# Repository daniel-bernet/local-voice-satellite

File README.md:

# Local Voice Satellite

A DIY voice satellite for [Home Assistant](https://www.home-assistant.io/): an ESP32-S3 with an I²S microphone, an I²S amplifier and an LED ring in a 3D-printed case. The wake word runs on the device. Speech-to-text and text-to-speech run on my own server. No audio goes to a cloud service.

<!-- PHOTO NEEDED: images/v2-hero.jpg: the assembled V2 satellite on a plain desk, LED ring lit amber, 3/4 front view from slightly above, neutral background, nothing else in frame. Replaces the render above. -->

This is a **portfolio showcase and a reference design**, not a kit. It documents one working build and the reasoning behind it: what I chose, why, what broke and what I'd do differently. It's meant for people who want to build something similar and are happy to make their own decisions. It is not a step-by-step tutorial.

## Why

I wanted a voice assistant for my home that works like a smart speaker but stays private: no always-listening cloud device, and no recordings leaving the house. Home Assistant's voice pipeline makes that possible with local speech-to-text and text-to-speech. What was missing was a satellite I understood end to end and could repair, so I built one.

## Result

The V2 satellite works. It hears "Hey Jarvis" on the device, Home Assistant turns the request into text and the answer into speech locally, and the answer plays on the satellite while the LED ring shows each stage. Simple requests take about 5–10 s end to end, down from about a minute right after assembly. I haven't measured the stage times yet. What V2 taught me (a mic mount that broke under the wire forces, speaker hiss, LEDs without a level shifter) went into a V3 PCB and case, which are designed and checked in code only, not built.

## Status

| Part | Status |
|---|---|
| **Satellite V2 (hand-wired)**: perfboard electronics in the V2 case | Built by me, working. Wake word, answers and audio all work. |
| **V2 enclosure** | Printed and assembled. Everything fit. |
| **V2 firmware** (ESPHome) | Running on the V2 satellite. The published copy is sanitised and passes ESPHome's config validation (2026.10.2). |
| **Satellite V3 (custom PCB)** | **Unverified design (rev A).** Designed, not fabricated, not tested, and it may never be built. Only code-level checks were run ([details](hardware/v3-pcb/README.md#what-was-checked)). |
| **V3 enclosure** | Unverified design, never printed. |
| **V3 firmware** | Draft for the unbuilt board. Passes ESPHome's config validation, never flashed. |
| **Voice pipeline**: on-device wake word, local STT (Whisper) and TTS (Piper) | Working. Observed end-to-end latency for simple requests (time, weather): **about 5–10 s**, down from about 1 min right after assembly. The stage times haven't been measured yet. |
| **LLM agent** for open questions | **Planned.** Not connected yet. |

### Next steps
- Measure the stage times (wake → end of speech → STT → intent → TTS) in Home Assistant's pipeline debug view, and only then decide what to optimise.
- Connect an LLM agent behind Home Assistant's built-in intents.
- Decide whether V3 gets built. If it does, start with the [must-verify list](hardware/v3-pcb/README.md#must-verify-before-ordering).

## Features

- **On-device wake word** ("Hey Jarvis", [micro_wake_word](https://esphome.io/components/micro_wake_word/)). Audio only streams to Home Assistant after the wake word.
- **Fully local pipeline**: Whisper for speech-to-text and Piper for text-to-speech, through Home Assistant's [Wyoming](https://www.home-assistant.io/integrations/wyoming/) integration.
- **LED ring state machine**: breathing while listening, a circling comet while thinking, a soft glow while answering, a red blink on errors and dim red while Home Assistant is disconnected. Every stage has a timeout, so the ring can't hang.
- **Amplifier power gating**: the amp's shutdown pin is driven by the firmware, so the speaker is silent between answers (no idle hiss).
- **Sealed speaker chamber** with TPU gaskets, the speaker firing upwards through a grille, and the mic on the front wall at 90° to it.
- **Designed as code**: the case is parametric [build123d](https://github.com/gumyr/build123d) code with automated collision, seal and assembly checks. The V3 PCB is generated by a Python toolkit into a KiCad 9 project.

## Architecture

```mermaid
flowchart LR
    subgraph SAT["Satellite (ESP32-S3)"]
        MIC["I²S mic"] --> WW["Wake word<br/>(micro_wake_word)"]
        LED["LED ring<br/>state machine"]
        SPK["I²S amp + speaker"]
    end
    WW -- "audio after wake word<br/>(ESPHome API, encrypted)" --> HA["Home Assistant<br/>Assist pipeline"]
    HA --> STT["Speech-to-text<br/>Whisper (Wyoming)"]
    STT --> INT["Built-in intents<br/>(time, weather, devices)"]
    INT -. "unmatched requests<br/>(planned)" .-> LLM["LLM agent<br/>(planned)"]
    INT --> TTS["Text-to-speech<br/>Piper (Wyoming)"]
    LLM -.-> TTS
    TTS -- "answer audio" --> SPK
    HA -- "pipeline events" --> LED
```

The diagram shows roles, not machines. More in [docs/architecture.md](docs/architecture.md).

## Hardware at a glance (V2, the working build)

| Part | Notes |
|---|---|
| ESP32-S3 devkit, N16R8 (16 MB flash, 8 MB octal PSRAM) | micro_wake_word needs the PSRAM |
| INMP441 I²S MEMS mic breakout (round) | I²S bus 0. End of life; the ICS-43434 is the usual replacement |
| MAX98357A I²S class-D amp breakout | I²S bus 1, gain 9 dB (GAIN pin open) |
| 40 mm full-range speaker | 40 × 40 mm flange, 32 mm hole pitch |
| WS2812B strip, 144 LED/m, 5 V | 40 LEDs (about 28 cm) around the inside of a clear plinth |
| USB-C PD trigger board, set to 5 V | one 5 V / GND star point for every module |
| 40 × 60 mm perfboard, 2 electrolytics (470 µF, 1000 µF), 10 kΩ × 2, 330 Ω | |
| M3 button-head screws (ISO 7380): 5 × M3×10, 4 × M3×8, 4 × M3×20 | threaded straight into PETG, no inserts |
| Filament: PETG black, PCTG clear, TPU black | printed on a Bambu Lab A1 mini, 0.4 mm nozzle |

Wiring diagram and pin table: [hardware/v2](hardware/v2/README.md). The V3 BOM with part numbers is in [hardware/v3-pcb/bom.csv](hardware/v3-pcb/bom.csv).

## Build and run

Tested with Python 3.12 and ESPHome 2026.10.2, from the repository root. The generators rewrite the committed outputs in place.

```bash
# Firmware: validate the V2 config. In secrets.yaml, replace the placeholder API key with a
# generated one (the command is in the file) and fill in your Wi-Fi details.
pip install esphome
cp firmware/esphome/secrets.example.yaml firmware/esphome/secrets.yaml
esphome config firmware/esphome/voice-satellite-v2.example.yaml

# V3 PCB (unverified design): regenerate, then read the outputs back with independent parsers
pip install shapely numpy matplotlib gerbonara kiutils
python3 hardware/v3-pcb/source/satellite_v3_pcb.py
python3 hardware/v3-pcb/source/check_outputs.py

# Cases: regenerate and check (V3 reads the board geometry written by the PCB step)
pip install build123d trimesh pyvista networkx
python3 enclosure/v2/source/case_v2.py && python3 enclosure/v2/source/check_case_v2.py
python3 enclosure/v3/source/case_v3.py && python3 enclosure/v3/source/check_case_v3.py
```

Flashing and adopting the device in Home Assistant: [firmware/esphome](firmware/esphome/README.md). Printing and assembly: [enclosure](enclosure/README.md) and [build notes](docs/build-notes.md). What reproduces exactly and what doesn't: [enclosure](enclosure/README.md#regenerate) and [V3 PCB](hardware/v3-pcb/README.md#files).

## Repository map

| Path | What's in it |
|---|---|
| [docs/](docs/) | [architecture](docs/architecture.md) · [design decisions](docs/design-decisions.md) · [wiring](docs/wiring.md) · [build notes](docs/build-notes.md) · [lessons learned](docs/lessons-learned.md) · [how it was built](docs/how-it-was-built.md) |
| [hardware/v2/](hardware/v2/README.md) | Hand-wired V2: wiring diagram (SVG) and pin table |
| [hardware/v3-pcb/](hardware/v3-pcb/README.md) | Custom PCB, **unverified rev A**: generator source, KiCad 9 project, Gerbers, BOM, renders, check report |
| [enclosure/](enclosure/README.md) | V2 (built) and V3 (unverified) cases: CAD source, STL in print orientation, STEP, renders, print settings |
| [firmware/esphome/](firmware/esphome/) | ESPHome example configs for V2 and V3 and a `secrets.example.yaml` |
| [images/](images/) | Photos (EXIF stripped) |

## How it was built

This project was built with AI assistance (Claude by Anthropic). I defined the requirements, chose the components, measured the real parts, specified and reviewed the designs, and printed, soldered, assembled and tested the hardware. The enclosure and the V3 PCB were generated **as code with AI assistance**, and the firmware, the wiring and soldering guides, the wiring diagram and the doc drafts were written with AI support. I reviewed, adapted and tested all of it. The full split of who did what is in [docs/how-it-was-built.md](docs/how-it-was-built.md).

## Licence

This is open source and permissive: you can copy, modify and sell it, as long as you keep the copyright and licence notices.

| What | Licence |
|---|---|
| Firmware configs and all code, including the PCB and CAD generators and check scripts (`firmware/`, `hardware/v3-pcb/source/`, `enclosure/*/source/`, except Markdown files) | [MIT](LICENSE) |
| Hardware designs: PCB, KiCad project, Gerbers, BOM, STL/STEP, check reports and the wiring diagram (rest of `hardware/` and `enclosure/`, except Markdown files and renders) | [CERN-OHL-P-2.0](LICENSES/CERN-OHL-P-2.0.txt) |
| Documentation and images: every Markdown file (`*.md`, including the READMEs in `firmware/`, `hardware/` and `enclosure/`), `docs/`, `images/` and all renders | [CC BY 4.0](LICENSES/CC-BY-4.0.txt) |

© 2026 Daniel Bernet. If you build on this, a credit or a link back is appreciated. GitHub's "Cite this repository" uses [CITATION.cff](CITATION.cff).

### Third-party

These are used or referenced, not bundled, and they keep their own licences:
- [ESPHome](https://esphome.io/): firmware framework the configs are written for.
- [micro_wake_word models](https://github.com/esphome/micro-wake-word-models): the `hey_jarvis` model is downloaded by ESPHome at build time (Apache-2.0).
- [Home Assistant](https://www.home-assistant.io/) with its Wyoming integration, Whisper and Piper: the voice pipeline on the server side.
- [KiCad](https://www.kicad.org/): opens the generated project. No KiCad library files are included; the footprints in `satellite.pretty` are re-created from datasheet dimensions by the generator.
- Python tools used to generate and check the designs: [build123d](https://github.com/gumyr/build123d), shapely, numpy, matplotlib, gerbonara, kiutils, trimesh, networkx, pyvista, cairosvg.
- Component datasheets are linked from [hardware/v3-pcb/README.md](hardware/v3-pcb/README.md#datasheets), not copied.

## Project page

The write-up of this project is on my site: [dbernet.ch/projects/local-voice-satellite](https://dbernet.ch/projects/local-voice-satellite/).

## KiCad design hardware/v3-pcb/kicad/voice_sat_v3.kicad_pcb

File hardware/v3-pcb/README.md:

# Satellite V3 (custom PCB): unverified design, rev A

> [!WARNING]
> **Unverified design (rev A).** This board has been **designed, not fabricated, not tested, and it may never be built.** It was generated as code and has only been checked in code (see [What was checked](#what-was-checked)). KiCad's own DRC has not been run, and the footprints for the ESP32 module and the USB-C receptacle are re-creations from datasheet dimensions. Treat it as the next iteration I designed after the lessons from V2, not as a finished product.

## What it is

A 100 × 72 mm, 2-layer main board that replaces V2's perfboard, devkit, PD trigger board, amp breakout and about 20 hand-run wires. A 27 × 24 mm mic carrier is attached as a breakaway with mouse bites, so the panel is 100 × 98 mm and fits the cheapest ≤ 100 × 100 mm fab tier. It fits the [V3 enclosure](../../enclosure/v3/), which is also unverified.

| Block | Parts | Notes |
|---|---|---|
| MCU | ESP32-S3-WROOM-1-N16R8 | antenna 4.3 mm over the left board edge, copper-free keep-out on both layers |
| USB-C | GCT USB4085-GF-A (through-hole), PTC 3 A, SMAJ5.0A TVS, USBLC6-2SC6 | 5.1 kΩ Rd on CC1/CC2 (no PD IC), CC voltage sensed on IO4/IO5, native USB on IO19/IO20 for flashing and logs |
| 3.3 V | TLV1117LV33 (AMS1117-3.3 footprint-compatible) | EN RC 10 kΩ / 1 µF, RESET and BOOT buttons |
| Audio out | MAX98357A (TQFN-16) with a 1 mm back-solder hole under the exposed pad | gain jumper, SD on IO7 with pull-down, speaker wires solder to two pads **inside** the sealed chamber |
| Mic | JST-PH 6 on the main board, mic module on the breakaway carrier | carrier screws to the front wall; SCK/WS/SD on IO11/IO12/IO13 |
| LEDs | 18 × WS2812B-5050 around the board edge, 74AHCT1G125 buffer | data on IO14, chain clockwise from the back-left; 5 V ring on the bottom layer |
| Bulk | 2 × 470 µF / 10 V radial | at the LED bus entry and near the amp |

**Firmware pin changes vs V2:** mic IO4/5/6 → IO11/12/13, amp IO15/16/17 → IO47/48/21, amp SD (IO7) and LED data (IO14) unchanged, CC sense on IO4/IO5 is new. Draft firmware: [voice-satellite-v3.example.yaml](../../firmware/esphome/voice-satellite-v3.example.yaml).

## What was checked

Run on 2026-11-15 when this repository was prepared, by regenerating everything from [source/](source/):

| Check | Tool | Result |
|---|---|---|
| Routing | pcbkit A* router | 0 failed connections |
| Geometric DRC: clearance 0.15 mm, copper-to-edge 0.3 mm, hole-to-hole 0.25 mm, annular ring 0.15 mm, courtyards | pcbkit (shapely) | **0 issues**. 12 notes at exactly 0.150 mm, all inside the USB-C receptacle's 0.85 mm pin field ([drc_report.txt](drc_report.txt)) |
| Connectivity, 47 nets | pcbkit | 46 nets are one copper island each. GND is the main plane plus 5 small pad-less fill pieces on the top layer (dead copper, largest about 19 mm²). **No GND pad or track is disconnected.** KiCad recomputes all fills on "Fill all zones". |
| Gerber read-back | gerbonara (independent parser), [source/check_outputs.py](source/check_outputs.py) | all 9 layers and both drill files parse (bottom paste is empty: no bottom SMD parts). Copper and silkscreen rendered and inspected ([renders/](renders/)). |
| KiCad file syntax | kiutils, [source/check_outputs.py](source/check_outputs.py) | `.kicad_pcb` (82 footprints, including 8 mouse-bite holes) and `.kicad_sch` (74 symbols) parse |
| Case fit | [enclosure/v3](../../enclosure/v3/) check script, using `board_for_case.json` | no collisions with the case model; the chamber gasket rim lands 100 % on the board |

**Not checked:** KiCad DRC/ERC, fab DFM review, footprint accuracy against the real parts, any electrical behaviour. None of it has been built.

**Found and fixed while preparing this repo:** the Gerber writer erased silkscreen text inside the speaker-chamber outline. A clear-polarity hole was written after the text it overlapped, and the generator now writes outer shapes first. The read-back render above was made after the fix.

**Known cosmetic issue (left as designed):** the module label "ESP32-S3-WROOM-1 N16R8 - antenna left" runs over the H4 mounting hole, so part of it is clipped on the silkscreen.

## Must-verify before ordering

1. Open `kicad/voice_sat_v3.kicad_pro` in KiCad 9 → **Edit → Fill all zones**, run **DRC**. Expect only the USB-C pin-field notes.
2. **Change Footprint** of U1 to `RF_Module:ESP32-S3-WROOM-1` and of J1 to `Connector_USB:USB_C_Receptacle_GCT_USB4085` from KiCad's own library, then re-run DRC. Keep the antenna over the left edge.
3. Confirm on the GCT drawing that the USB4085's front face sits **2.5 mm past the board edge** (an estimate here) and that the body is 3.46 mm high. The case cutout depends on both.
4. Check the mic module's pin order against the carrier silkscreen, and the speaker polarity.
5. **Re-plot the Gerbers from KiCad** (File → Fabrication Outputs) and order those. The Gerbers in [gerbers/](gerbers/) come straight from the generator and are meant as a cross-check.

**Intended order settings:** 2 layers, FR4 1.6 mm, 1 oz copper, HASL lead-free, tented vias, no stencil (hand soldering).
**Rough cost estimate (not quoted):** CHF 25–45 for a batch of 5–10 boards including shipping, plus about CHF 25–35 in parts per board.

## Hand-soldering plan (iron only, untested)

1. Small SMD parts first (0805, SOT-23, SOT-223, SMA, 1812), with plenty of flux.
2. U4 MAX98357A (TQFN-16): tin the pads lightly, place, drag-solder each side, then heat the exposed pad through the 1 mm hole from the back until solder wicks through.
3. U1 module: tack two corner castellations, then solder the rest. The 1.8 mm hole under the EPAD is optional (ground/thermal only).
4. LEDs: the cut corner is pin 1 (VDD). Keep the iron under 2 s per pad.
5. Through-hole parts last: USB-C (0.85 mm pitch, solder the shell stakes well because they take the plug force), JST, buttons, capacitors.
6. Bring-up: only the LDO and its passives → check 3.3 V; then the module → the PC should see a USB serial device; then the rest.

## Files

| Path | Content |
|---|---|
| [source/pcbkit.py](source/pcbkit.py) | PCB-as-code toolkit: footprints, router, zones, DRC, KiCad 9 and Gerber writers (MIT) |
| [source/satellite_v3_pcb.py](source/satellite_v3_pcb.py) | The board: parts, nets, placement, routing order, outputs (MIT) |
| [source/check_outputs.py](source/check_outputs.py) | Independent read-back of the Gerbers, drill files and KiCad files (MIT) |
| [kicad/](kicad/) | KiCad 9 project, PCB, machine-generated schematic, `satellite.pretty` footprint library |
| [gerbers/](gerbers/) | RS-274X and Excellon (slots as G85) from the generator |
| [bom.csv](bom.csv), [positions.csv](positions.csv) | BOM with part numbers, placement |
| [drc_report.txt](drc_report.txt) | Output of the geometric DRC |
| [board_for_case.json](board_for_case.json) | Outline, holes and part envelopes for the case script |
| [renders/](renders/) | Copper overlay renders (SVG from the generator, PNG copies) and Gerber read-back renders |

Regenerate with `pip install shapely numpy matplotlib` and then `python3 source/satellite_v3_pcb.py` (about 25 s). It writes the KiCad project, Gerbers, drill files, BOM, positions, DRC report, `board_for_case.json` and the two SVG renders. Router and DRC are deterministic: a fresh run reproduces all of these byte for byte, except that the KiCad files get new UUIDs on every run.

Repeat the read-back with `pip install gerbonara kiutils` and `python3 source/check_outputs.py`. It prints what each file parses to and writes read-back SVG renders of both sides to `build/` (git-ignored). The PNG files in [renders/](renders/) were made once from the SVGs and the read-back while this repository was prepared; no script here regenerates them.

## Datasheets

Linked, not copied:
- [ESP32-S3-WROOM-1 datasheet](https://documentation.espressif.com/esp32-s3-wroom-1_wroom-1u_datasheet_en.pdf) and the [Espressif ESP32-S3 PCB layout guide](https://docs.espressif.com/projects/esp-hardware-design-guidelines/en/latest/esp32s3/pcb-layout-design.html)
- [GCT USB4085](https://gct.co/connector/usb4085)
- [MAX98357A datasheet (Analog Devices)](https://www.analog.com/media/en/technical-documentation/data-sheets/MAX98357A-MAX98357B.pdf)
- [ICS-43434 datasheet](https://www.farnell.com/datasheets/2632666.pdf)
- [PCBWay capabilities](https://www.pcbway.com/capabilities.html), used for the design rules

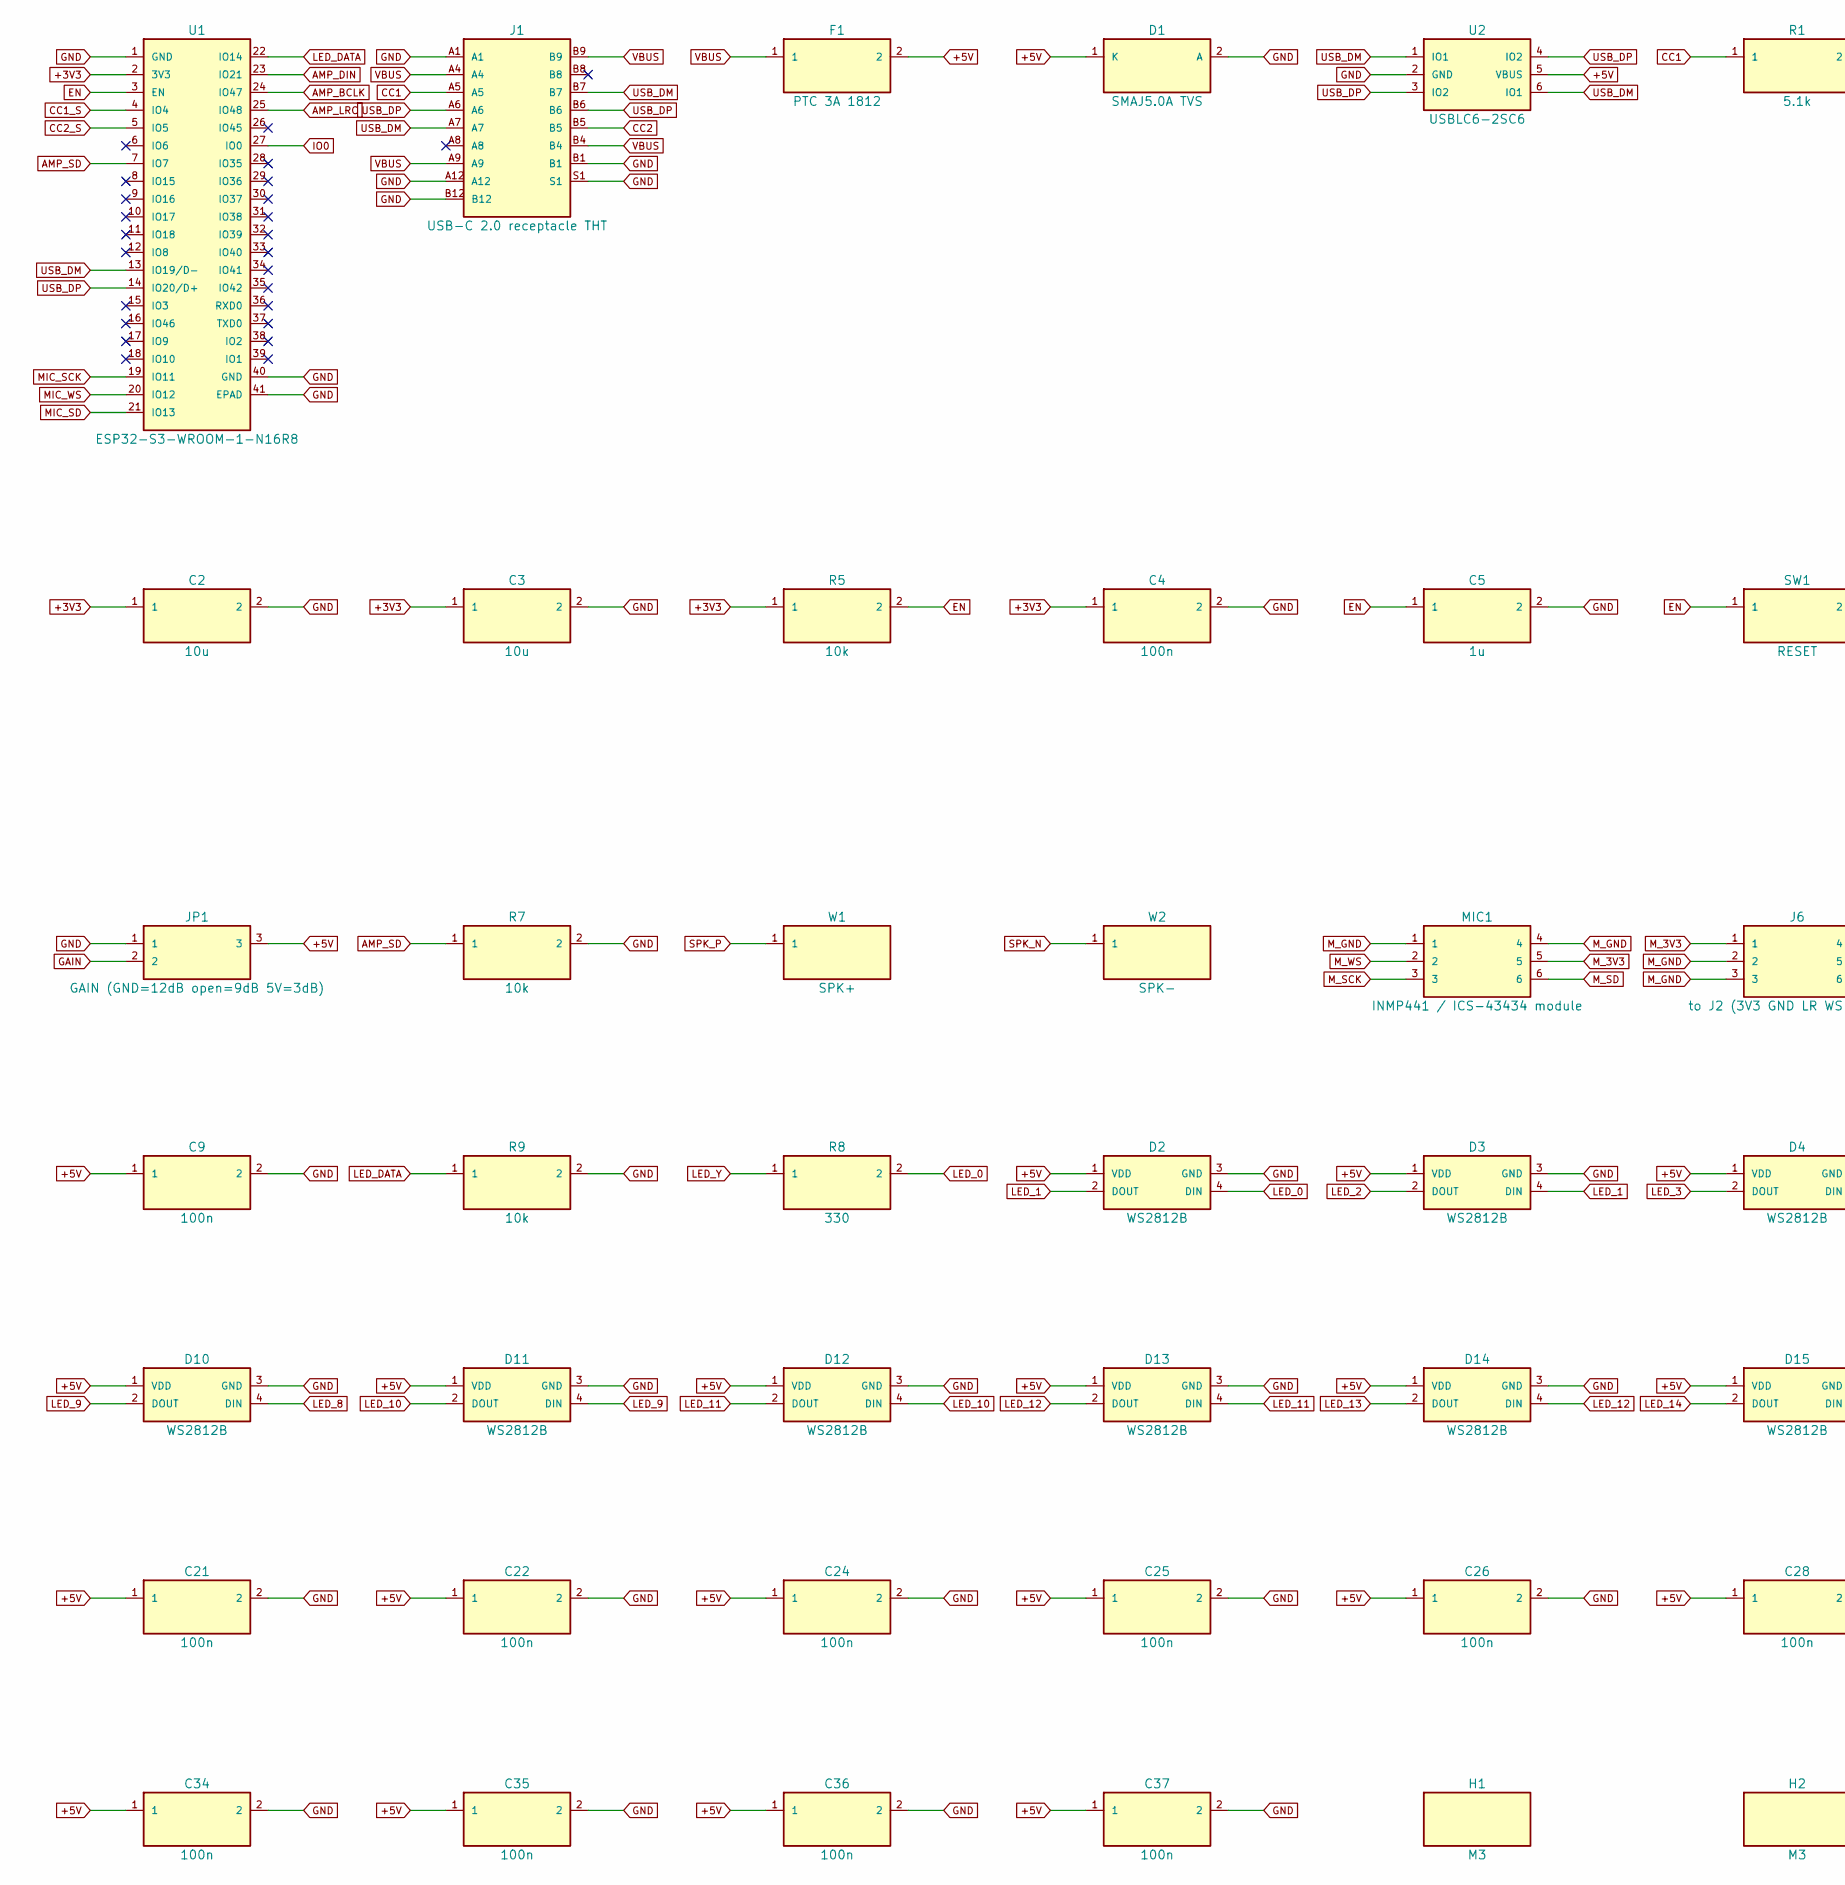
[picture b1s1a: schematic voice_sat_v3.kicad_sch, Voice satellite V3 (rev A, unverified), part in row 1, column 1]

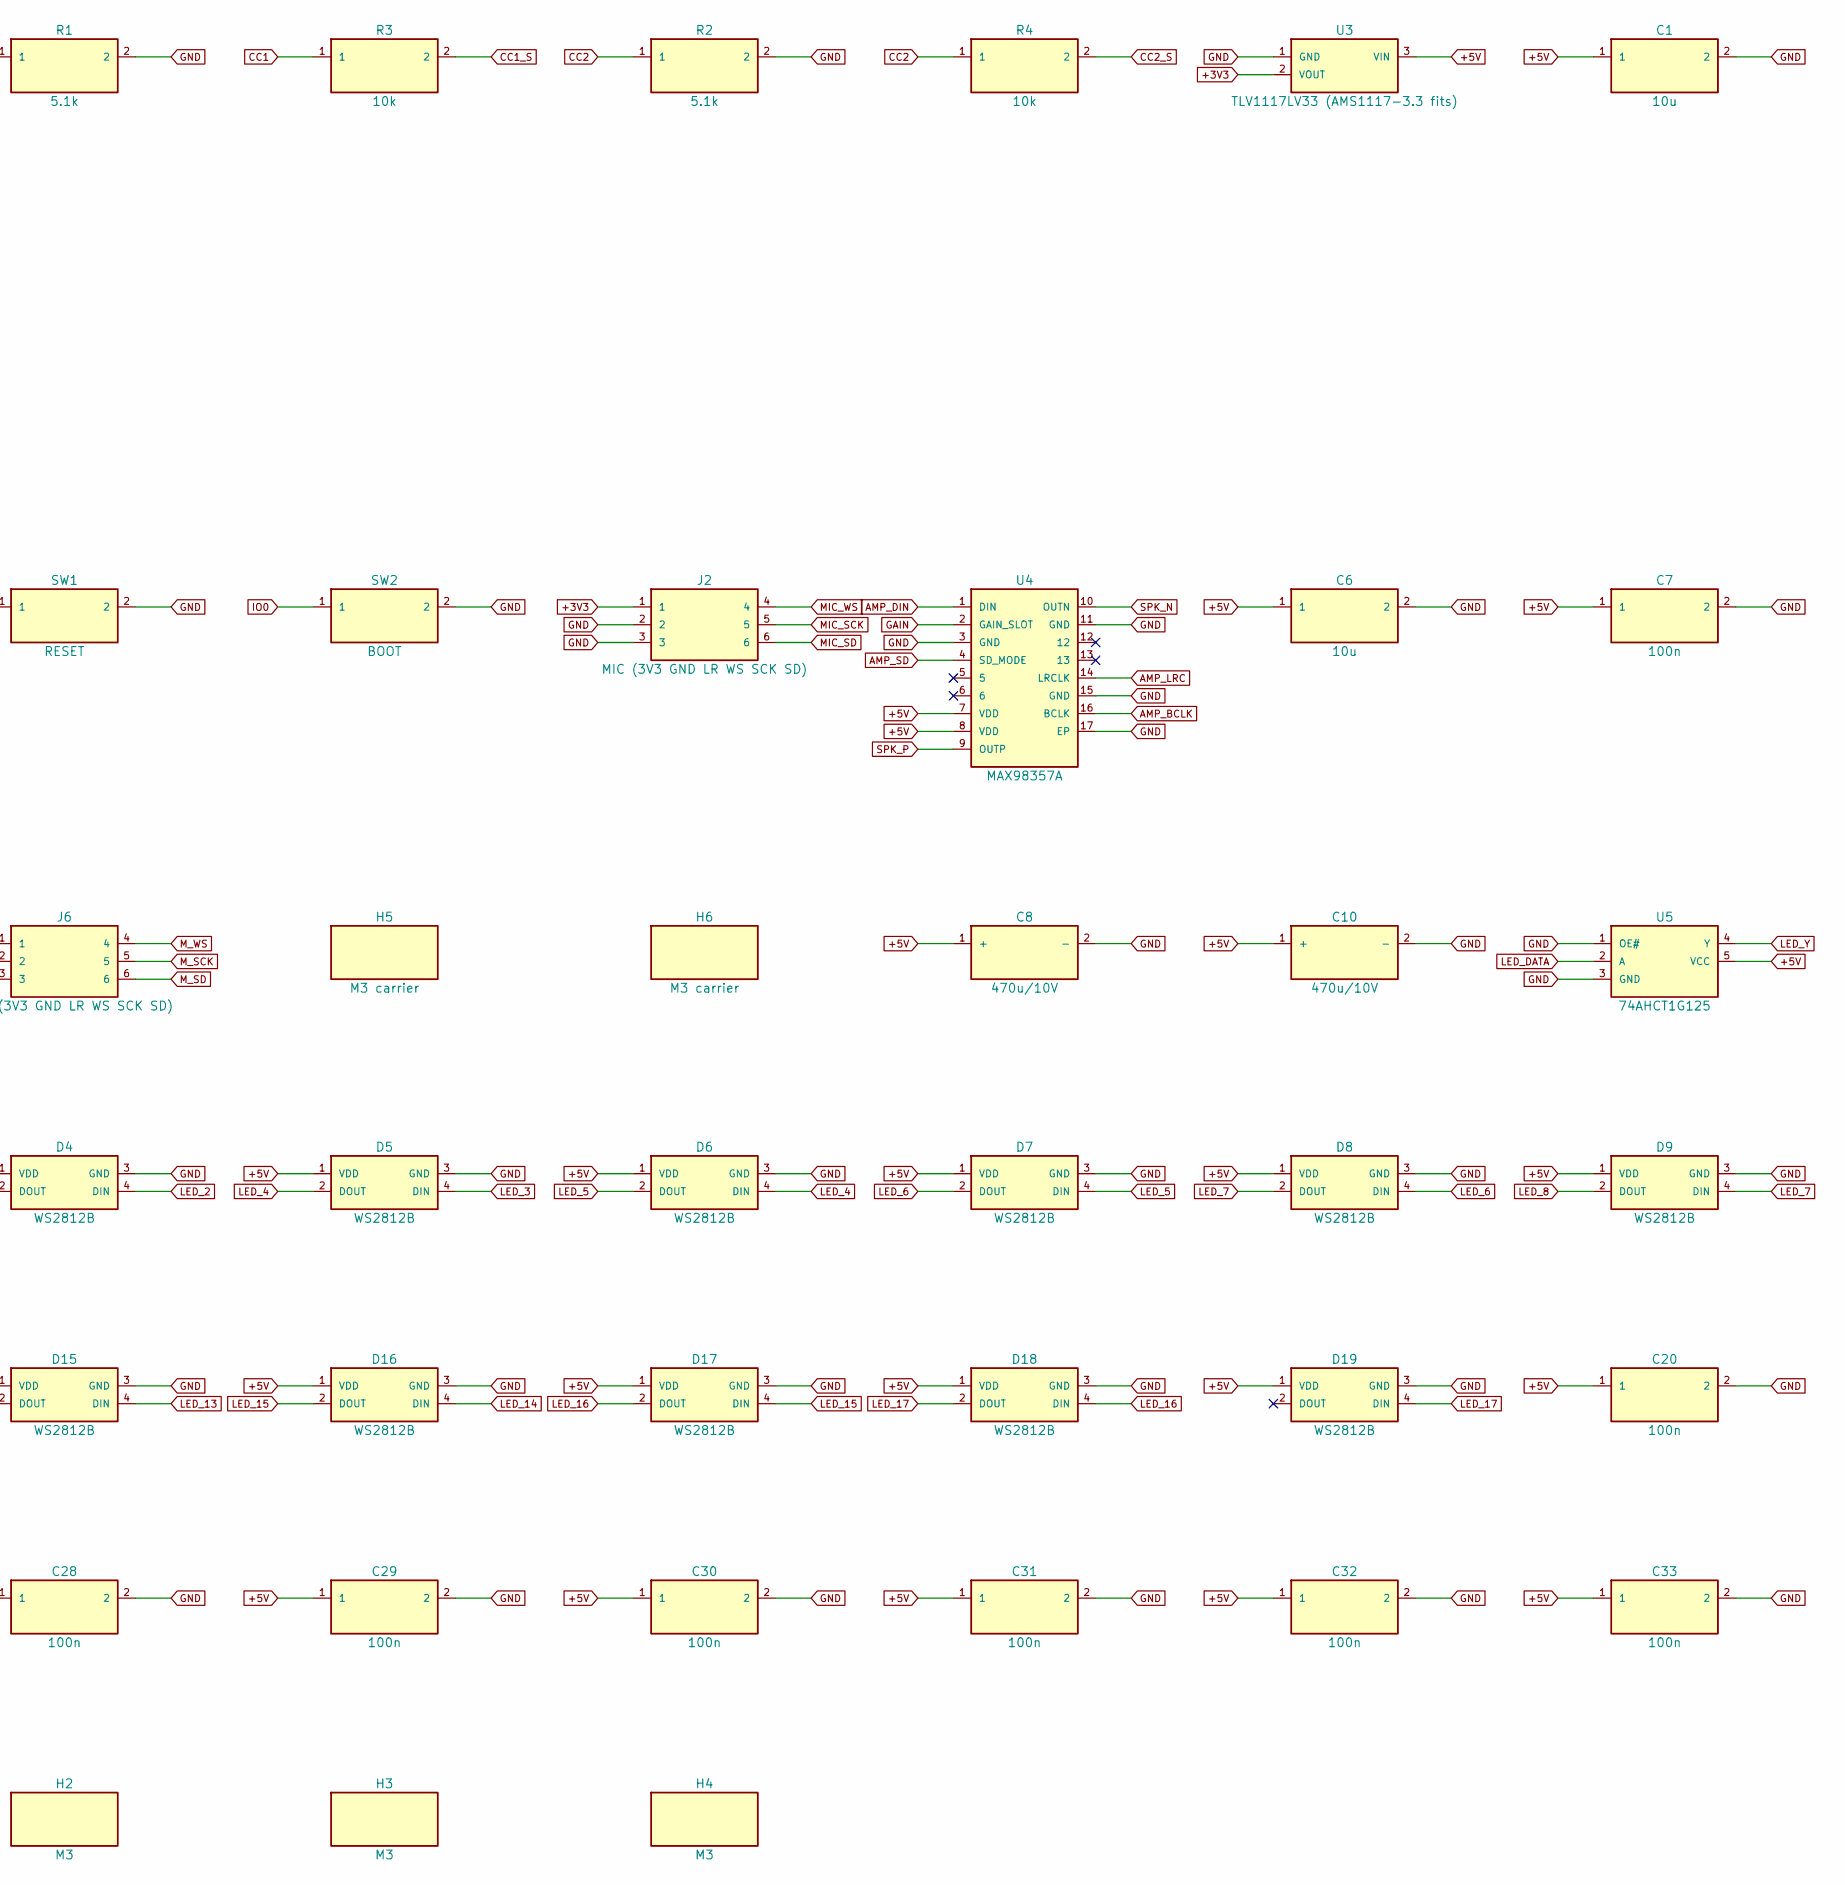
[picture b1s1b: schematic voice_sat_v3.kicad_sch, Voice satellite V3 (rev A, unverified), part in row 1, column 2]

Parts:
C1, C2, C3, C6: 10u; C_0805
C4, C7, C9, C20, C21, C22, C24, C25, C26, C28, C29, C30, C31, C32, C33, C34, C35, C36, C37: 100n; C_0805
C5: 1u; C_0805
C8, C10: 470u/10V; CP_Radial_D8.0
D1: SMAJ5.0A TVS; D_SMA
D2, D3, D4, D5, D6, D7, D8, D9, D10, D11, D12, D13, D14, D15, D16, D17, D18, D19: WS2812B; LED_WS2812B_5050
F1: PTC 3A 1812; C_1812
H1, H2, H3, H4: M3; MountingHole_3.2
H5, H6: M3 carrier; MountingHole_3.2
J1: USB-C 2.0 receptacle THT; USB_C_GCT_USB4085
J2: MIC (3V3 GND LR WS SCK SD); JST_PH_B6B
J6: to J2 (3V3 GND LR WS SCK SD); JST_PH_B6B
JP1: GAIN (GND=12dB open=9dB 5V=3dB); SolderJumper_3
MIC1: INMP441 / ICS-43434 module; MIC_Module_D14_2x3
R1, R2: 5.1k; C_0805
R3, R4, R5, R7, R9: 10k; C_0805
R8: 330; C_0805
SW1: RESET; SW_Tact_6x6
SW2: BOOT; SW_Tact_6x6
U1: ESP32-S3-WROOM-1-N16R8; ESP32-S3-WROOM-1
U2: USBLC6-2SC6; SOT-23-6
U3: TLV1117LV33 (AMS1117-3.3 fits); SOT-223
U4: MAX98357A; TQFN-16_3x3
U5: 74AHCT1G125; SOT-23-5
W1: SPK+; WirePad_3.0x2.5
W2: SPK-; WirePad_3.0x2.5

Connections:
+3V3: C2.1, C3.1, C4.1, J2.1, R5.1, U1.2 (3V3), U3.2 (VOUT)
+5V: C1.1, C6.1, C7.1, C8.1 (+), C9.1, C10.1 (+), C20.1, C21.1, C22.1, C24.1, C25.1, C26.1, C28.1, C29.1, C30.1, C31.1, C32.1, C33.1, C34.1, C35.1, C36.1, C37.1, D1.1 (K), D2.1 (VDD), D3.1 (VDD), D4.1 (VDD), D5.1 (VDD), D6.1 (VDD), D7.1 (VDD), D8.1 (VDD), D9.1 (VDD), D10.1 (VDD), D11.1 (VDD), D12.1 (VDD), D13.1 (VDD), D14.1 (VDD), D15.1 (VDD), D16.1 (VDD), D17.1 (VDD), D18.1 (VDD), D19.1 (VDD), F1.2, JP1.3, U2.5 (VBUS), U3.3 (VIN), U4.7 (VDD), U4.8 (VDD), U5.5 (VCC)
AMP_BCLK: U1.24 (IO47), U4.16 (BCLK)
AMP_DIN: U1.23 (IO21), U4.1 (DIN)
AMP_LRC: U1.25 (IO48), U4.14 (LRCLK)
AMP_SD: R7.1, U1.7 (IO7), U4.4 (SD_MODE)
CC1: J1.A5, R1.1, R3.1
CC1_S: R3.2, U1.4 (IO4)
CC2: J1.B5, R2.1, R4.1
CC2_S: R4.2, U1.5 (IO5)
EN: C5.1, R5.2, SW1.1, U1.3 (EN)
GAIN: JP1.2, U4.2 (GAIN_SLOT)
GND: C1.2, C2.2, C3.2, C4.2, C5.2, C6.2, C7.2, C8.2 (-), C9.2, C10.2 (-), C20.2, C21.2, C22.2, C24.2, C25.2, C26.2, C28.2, C29.2, C30.2, C31.2, C32.2, C33.2, C34.2, C35.2, C36.2, C37.2, D1.2 (A), D2.3 (GND), D3.3 (GND), D4.3 (GND), D5.3 (GND), D6.3 (GND), D7.3 (GND), D8.3 (GND), D9.3 (GND), D10.3 (GND), D11.3 (GND), D12.3 (GND), D13.3 (GND), D14.3 (GND), D15.3 (GND), D16.3 (GND), D17.3 (GND), D18.3 (GND), D19.3 (GND), J1.A1, J1.A12, J1.B1, J1.B12, J1.S1, J2.2, J2.3, JP1.1, R1.2, R2.2, R7.2, R9.2, SW1.2, SW2.2, U1.1 (GND), U1.40 (GND), U1.41 (EPAD), U2.2 (GND), U3.1 (GND), U4.3 (GND), U4.11 (GND), U4.15 (GND), U4.17 (EP), U5.1 (OE#), U5.3 (GND)
IO0: SW2.1, U1.27 (IO0)
LED_0: D2.4 (DIN), R8.2
LED_1: D2.2 (DOUT), D3.4 (DIN)
LED_2: D3.2 (DOUT), D4.4 (DIN)
LED_3: D4.2 (DOUT), D5.4 (DIN)
LED_4: D5.2 (DOUT), D6.4 (DIN)
LED_5: D6.2 (DOUT), D7.4 (DIN)
LED_6: D7.2 (DOUT), D8.4 (DIN)
LED_7: D8.2 (DOUT), D9.4 (DIN)
LED_8: D9.2 (DOUT), D10.4 (DIN)
LED_9: D10.2 (DOUT), D11.4 (DIN)
LED_10: D11.2 (DOUT), D12.4 (DIN)
LED_11: D12.2 (DOUT), D13.4 (DIN)
LED_12: D13.2 (DOUT), D14.4 (DIN)
LED_13: D14.2 (DOUT), D15.4 (DIN)
LED_14: D15.2 (DOUT), D16.4 (DIN)
LED_15: D16.2 (DOUT), D17.4 (DIN)
LED_16: D17.2 (DOUT), D18.4 (DIN)
LED_17: D18.2 (DOUT), D19.4 (DIN)
LED_DATA: R9.1, U1.22 (IO14), U5.2 (A)
LED_Y: R8.1, U5.4 (Y)
MIC_SCK: J2.5, U1.19 (IO11)
MIC_SD: J2.6, U1.21 (IO13)
MIC_WS: J2.4, U1.20 (IO12)
M_3V3: J6.1, MIC1.5
M_GND: J6.2, J6.3, MIC1.1, MIC1.4
M_SCK: J6.5, MIC1.3
M_SD: J6.6, MIC1.6
M_WS: J6.4, MIC1.2
SPK_N: U4.10 (OUTN), W2.1
SPK_P: U4.9 (OUTP), W1.1
USB_DM: J1.A7, J1.B7, U1.13 (IO19/D-), U2.1 (IO1), U2.6 (IO1)
USB_DP: J1.A6, J1.B6, U1.14 (IO20/D+), U2.3 (IO2), U2.4 (IO2)
VBUS: F1.1, J1.A4, J1.A9, J1.B4, J1.B9

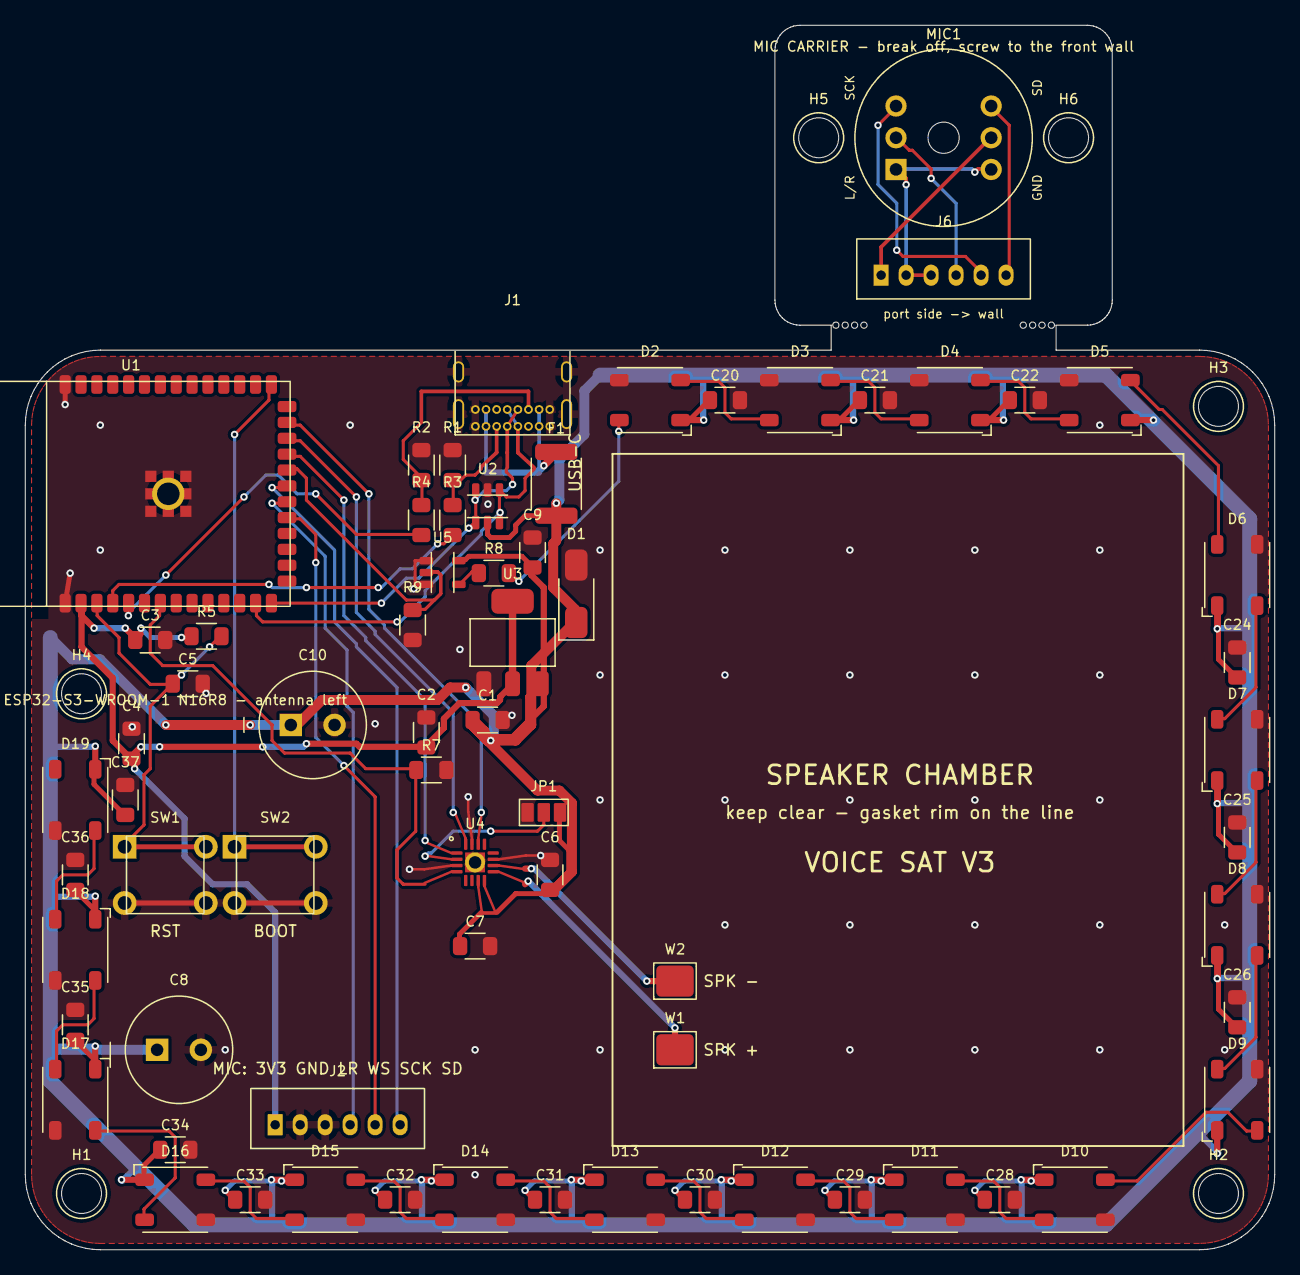
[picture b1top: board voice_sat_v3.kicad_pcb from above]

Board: 2 copper layers, 100.0 x 98.0 mm, 74 parts (0 on the bottom side), 47 nets.

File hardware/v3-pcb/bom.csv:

Qty,Refs,Value,Footprint,MPN,DNP
4,"C1 C2 C3 C6","10u",C_0805,"",
19,"C20 C21 C22 C24 C25 C26 C28 C29 C30 C31 C32 C33 C34 C35 C36 C37 C4 C7 C9","100n",C_0805,"",
1,"C5","1u",C_0805,"",
2,"C10 C8","470u/10V",CP_Radial_D8.0,"",
1,"D1","SMAJ5.0A TVS",D_SMA,"SMAJ5.0A",
18,"D10 D11 D12 D13 D14 D15 D16 D17 D18 D19 D2 D3 D4 D5 D6 D7 D8 D9","WS2812B",LED_WS2812B_5050,"WS2812B-V5",
1,"F1","PTC 3A 1812",C_1812,"Bel 0ZCJ0300FF2E (any 1812 3 A PTC)",
4,"H1 H2 H3 H4","M3",MountingHole_3.2,"",
2,"H5 H6","M3 carrier",MountingHole_3.2,"",
1,"J1","USB-C 2.0 receptacle THT",USB_C_GCT_USB4085,"GCT USB4085-GF-A",
1,"J2","MIC (3V3 GND LR WS SCK SD)",JST_PH_B6B,"JST B6B-PH-K-S",
1,"J6","to J2 (3V3 GND LR WS SCK SD)",JST_PH_B6B,"JST B6B-PH-K-S",
1,"JP1","GAIN (GND=12dB open=9dB 5V=3dB)",SolderJumper_3,"",
1,"MIC1","INMP441 / ICS-43434 module",MIC_Module_D14_2x3,"",
2,"R1 R2","5.1k",C_0805,"",
5,"R3 R4 R5 R7 R9","10k",C_0805,"",
1,"R8","330",C_0805,"",
1,"SW1","RESET",SW_Tact_6x6,"",
1,"SW2","BOOT",SW_Tact_6x6,"",
1,"U1","ESP32-S3-WROOM-1-N16R8",ESP32-S3-WROOM-1,"ESP32-S3-WROOM-1-N16R8",
1,"U2","USBLC6-2SC6",SOT-23-6,"USBLC6-2SC6",
1,"U3","TLV1117LV33 (AMS1117-3.3 fits)",SOT-223,"TLV1117LV33DCYR",
1,"U4","MAX98357A",TQFN-16_3x3,"MAX98357AETE+T",
1,"U5","74AHCT1G125",SOT-23-5,"SN74AHCT1G125DBVR",
1,"W1","SPK+",WirePad_3.0x2.5,"",
1,"W2","SPK-",WirePad_3.0x2.5,"",

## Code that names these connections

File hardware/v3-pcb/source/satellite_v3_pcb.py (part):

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P("SW2", FP["tact"], 20.0, 30.0, 0, "BOOT", {"1": "IO0", "2": "GND"})

# microphone connector (ICS-43434 / INMP441 module on the carrier, JST-PH pigtail)
P("J2", FP["ph6"], 25.0, 10.0, 0, "MIC (3V3 GND LR WS SCK SD)", {"1": "+3V3", "2": "GND", "3": "GND", "4": "MIC_WS", "5": "MIC_SCK", "6": "MIC_SD"}, mfr="JST B6B-PH-K-S")

# amplifier (bare chip)
amp_nets = {"1": "AMP_DIN", "2": "GAIN", "3": "GND", "4": "AMP_SD", "7": "+5V", "8": "+5V", "9": "SPK_P", "10": "SPK_N", "11": "GND",
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# mic carrier (breakaway): module pads, JST-PH 6 to the main board's J2 (1:1 pigtail), 2x M3 for inserts in the wall bosses
mic_nets = {"1": "M_GND", "2": "M_WS", "3": "M_SCK", "4": "M_GND", "5": "M_3V3", "6": "M_SD"}   # A: L/R WS SCK (top->bottom)  B: GND VDD SD
P("MIC1", FP["mic"], 73.5, 89.0, 0, "INMP441 / ICS-43434 module", mic_nets)
P("J6", FP["ph6"], 73.5, 78.0, 0, "to J2 (3V3 GND LR WS SCK SD)", {"1": "M_3V3", "2": "M_GND", "3": "M_GND", "4": "M_WS", "5": "M_SCK", "6": "M_SD"}, mfr="JST B6B-PH-K-S")
P("H5", FP["hole"], 63.5, 89.0, 0, "M3 carrier", {})
P("H6", FP["hole"], 83.5, 89.0, 0, "M3 carrier", {})
P("C8", FP["radial"], 12.3, 16.0, 0, "470u/10V", {"1": "+5V", "2": "GND"})
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

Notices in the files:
hardware/v3-pcb/source/satellite_v3_pcb.py:
SPDX-License-Identifier: MIT
Copyright (c) 2026 Daniel Bernet
